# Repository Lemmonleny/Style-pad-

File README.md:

# Style-pad-
An open-source macro pad I made for 2026 stardance challenge. It's simple, backlit, 8 keyed, with a rotary encoder and a screen to keep you company! 
It took me a little over 17 hours to make.

PCB

Schematic

case

case together

NOTES

Well it wasint easy, but I got a whole lot better at CAD, I learned how to make PCB, and I learned QMK.

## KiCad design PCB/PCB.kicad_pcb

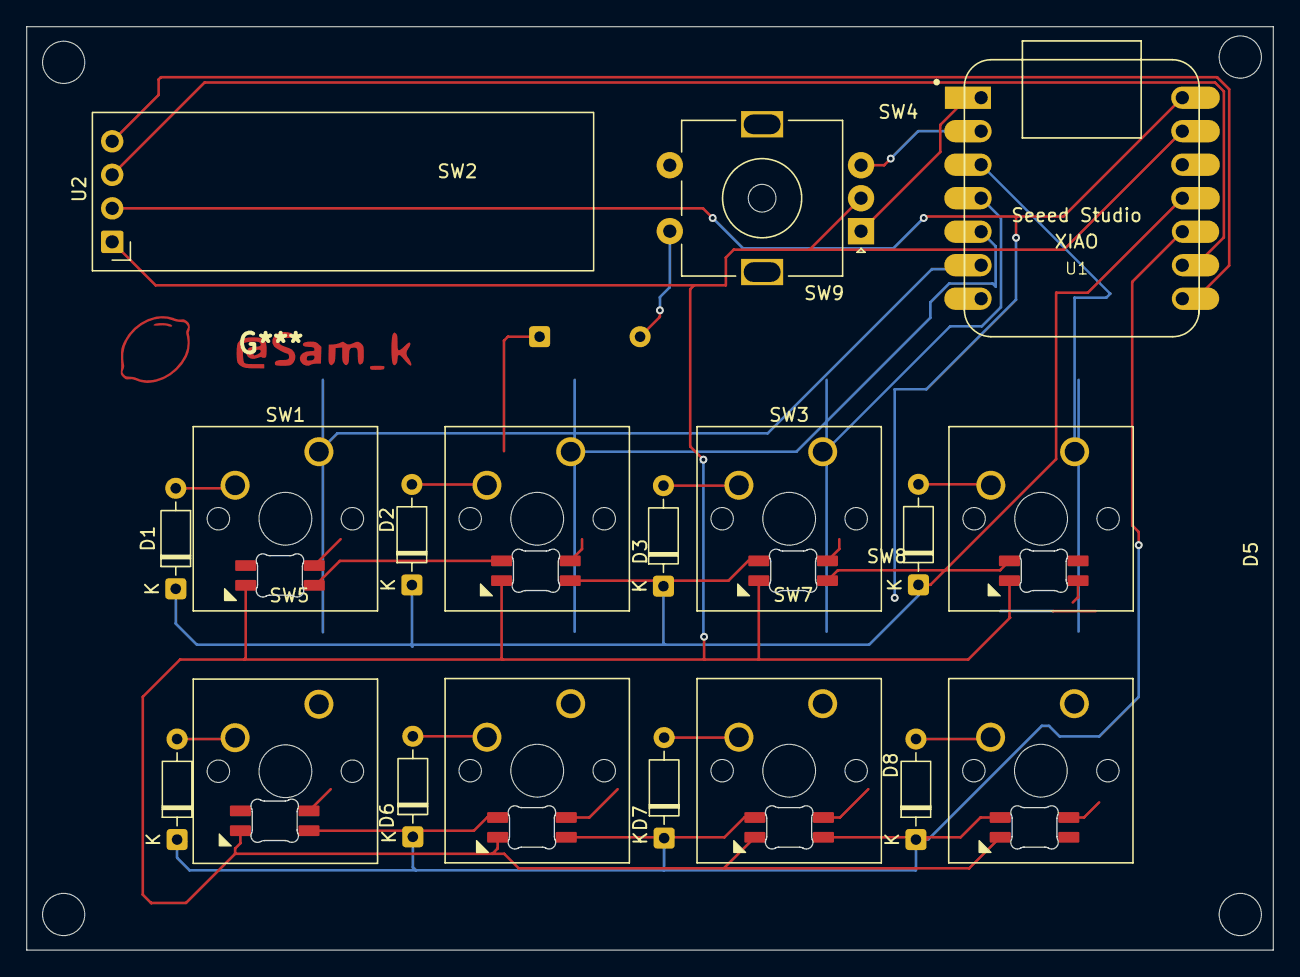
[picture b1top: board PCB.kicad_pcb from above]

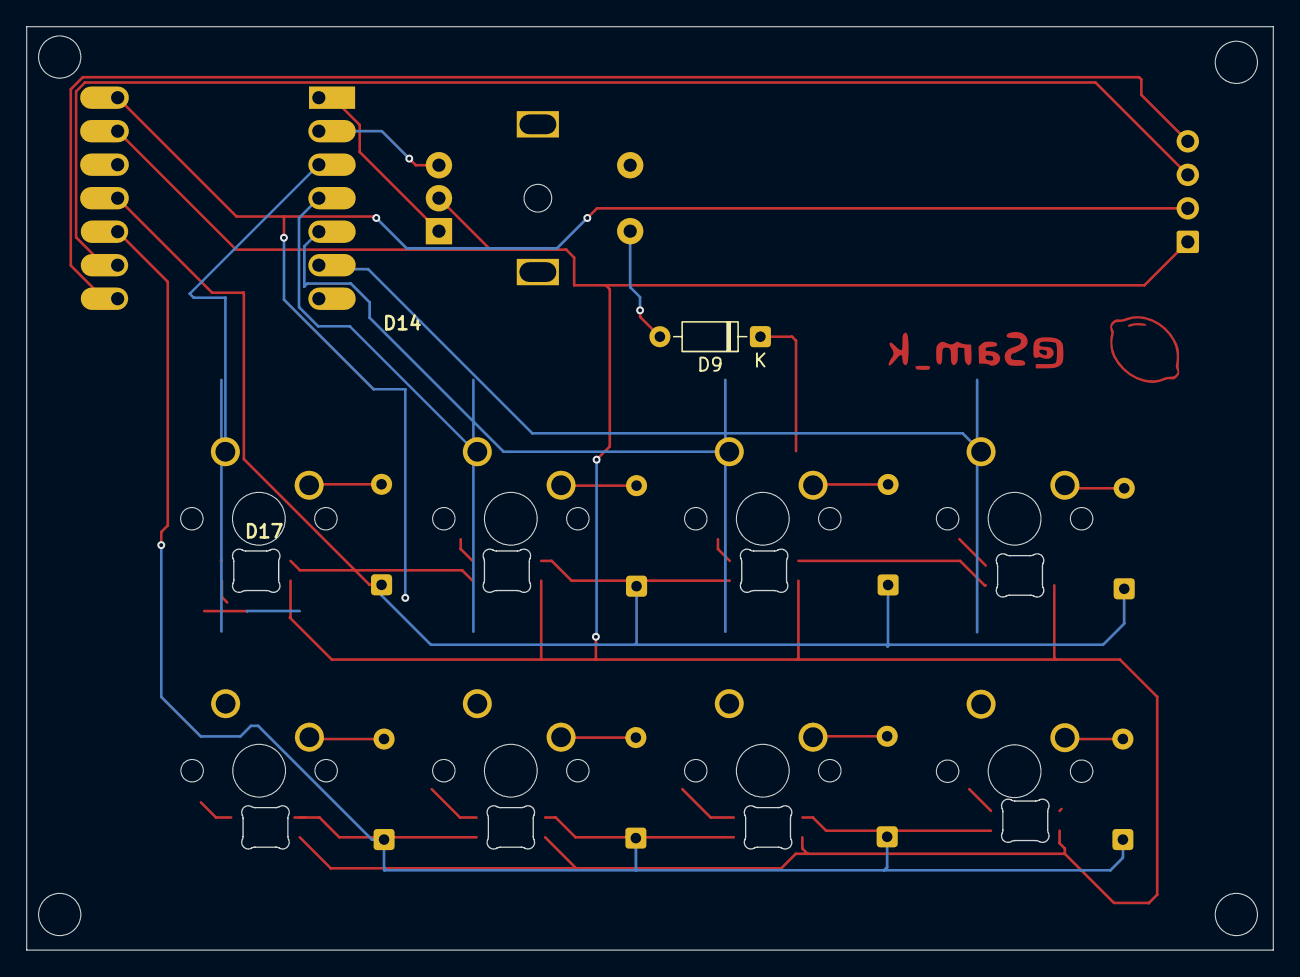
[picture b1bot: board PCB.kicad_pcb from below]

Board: 2 copper layers, 94.5 x 70.0 mm, 28 parts (9 on the bottom side), 29 nets.

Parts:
D1, D2, D3, D4, D5, D6, D7, D8, D9: 1N4148; D_DO-35_SOD27_P7.62mm_Horizontal
D10, D11, D12, D13, D14, D15, D16, D17: SK6812MINI-E; SK6812MINI-E_fixed
SW1, SW2, SW3, SW4, SW5, SW6, SW7, SW8: SW_Push; SW_Cherry_MX_1.00u_PCB
SW9: RotaryEncoder_Switch; RotaryEncoder_Alps_EC11E-Switch_Vertical_H20mm_MountingHoles
U1: MOUDLE-SEEEDUINO-XIAO; XIAO-Generic-Hybrid-14P-2.54-21X17.8MM
U2: ER_OLEDM0.91_1x-I2C

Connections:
/Coloum 0: SW4.1, SW8.1, U1.3 (PA10_A2_D2)
/Coloum 1: SW3.1, SW7.1, U1.4 (PA11_A3_D3)
/Coloum 2: SW2.1, SW6.1, U1.5 (PA8_A4_D4_SDA)
/Coloum 3: SW1.1, SW5.1, U1.6 (PA9_A5_D5_SCL)
/EC11A: SW9.A, U1.1 (PA02_A0_D0)
/EC11B: SW9.B, U1.2 (PA4_A1_D1)
/EC111: D9.2 (A), SW9.S2
/Row 1: D1.1 (K), D2.1 (K), D3.1 (K), D4.1 (K), D9.1 (K), U1.11 (PA6_A10_D10_MOSI)
/Row 2: D5.1 (K), D6.1 (K), D7.1 (K), D8.1 (K), U1.10 (PA5_A9_D9_MISO)
/SK6812: D10.4 (DIN), U1.7 (PB08_A6_D6_TX)
/scl: U1.9 (PA7_A8_D8_SCK), U2.3 (SCL)
/sda: U1.8 (PB09_A7_D7_RX), U2.4 (SDA)
GND: D10.3 (VSS), D11.3 (VSS), D12.3 (VSS), D13.3 (VSS), D14.3 (VSS), D15.3 (VSS), D16.3 (VSS), D17.3 (VSS), SW9.C, U1.13 (GND), U2.1 (GND)
unnamed: D1.2 (A), SW1.2
unnamed: D2.2 (A), SW2.2
unnamed: D3.2 (A), SW3.2
unnamed: D4.2 (A), SW4.2
unnamed: D5.2 (A), SW5.2
unnamed: D6.2 (A), SW6.2
unnamed: D7.2 (A), SW7.2
unnamed: D8.2 (A), SW8.2
unnamed: D10.2 (DOUT), D11.4 (DIN)
unnamed: D11.2 (DOUT), D12.4 (DIN)
unnamed: D12.2 (DOUT), D17.4 (DIN)
unnamed: D13.4 (DIN), D17.2 (DOUT)
unnamed: D13.2 (DOUT), D14.4 (DIN)
unnamed: D14.2 (DOUT), D15.4 (DIN)
unnamed: D15.2 (DOUT), D16.4 (DIN)
VCC: D10.1 (VDD), D11.1 (VDD), D12.1 (VDD), D13.1 (VDD), D14.1 (VDD), D15.1 (VDD), D16.1 (VDD), D17.1 (VDD), U1.14 (5V), U2.2 (VCC)
